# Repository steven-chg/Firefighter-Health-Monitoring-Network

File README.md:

# Firefighter Health Monitoring Network

A wearable health monitoring system that enables real-time tracking of firefighters' vital signs and environmental conditions during active duty. The system utilizes a mesh network of ESP32-based devices to continuously monitor and transmit critical health data including:

- Heart rate
- Motion 
- GPS location tracking
- Surrounding temperature measurements

## Key Features
- Wearable sensors integrated into firefighter gear
- Central monitoring hub for incident commanders with intuitive GUI 
- Real-time alerts for abnormal vital signs
- Mesh network with 300m+ urban range
- 2+ hour battery life in high temperature conditions

## Demo

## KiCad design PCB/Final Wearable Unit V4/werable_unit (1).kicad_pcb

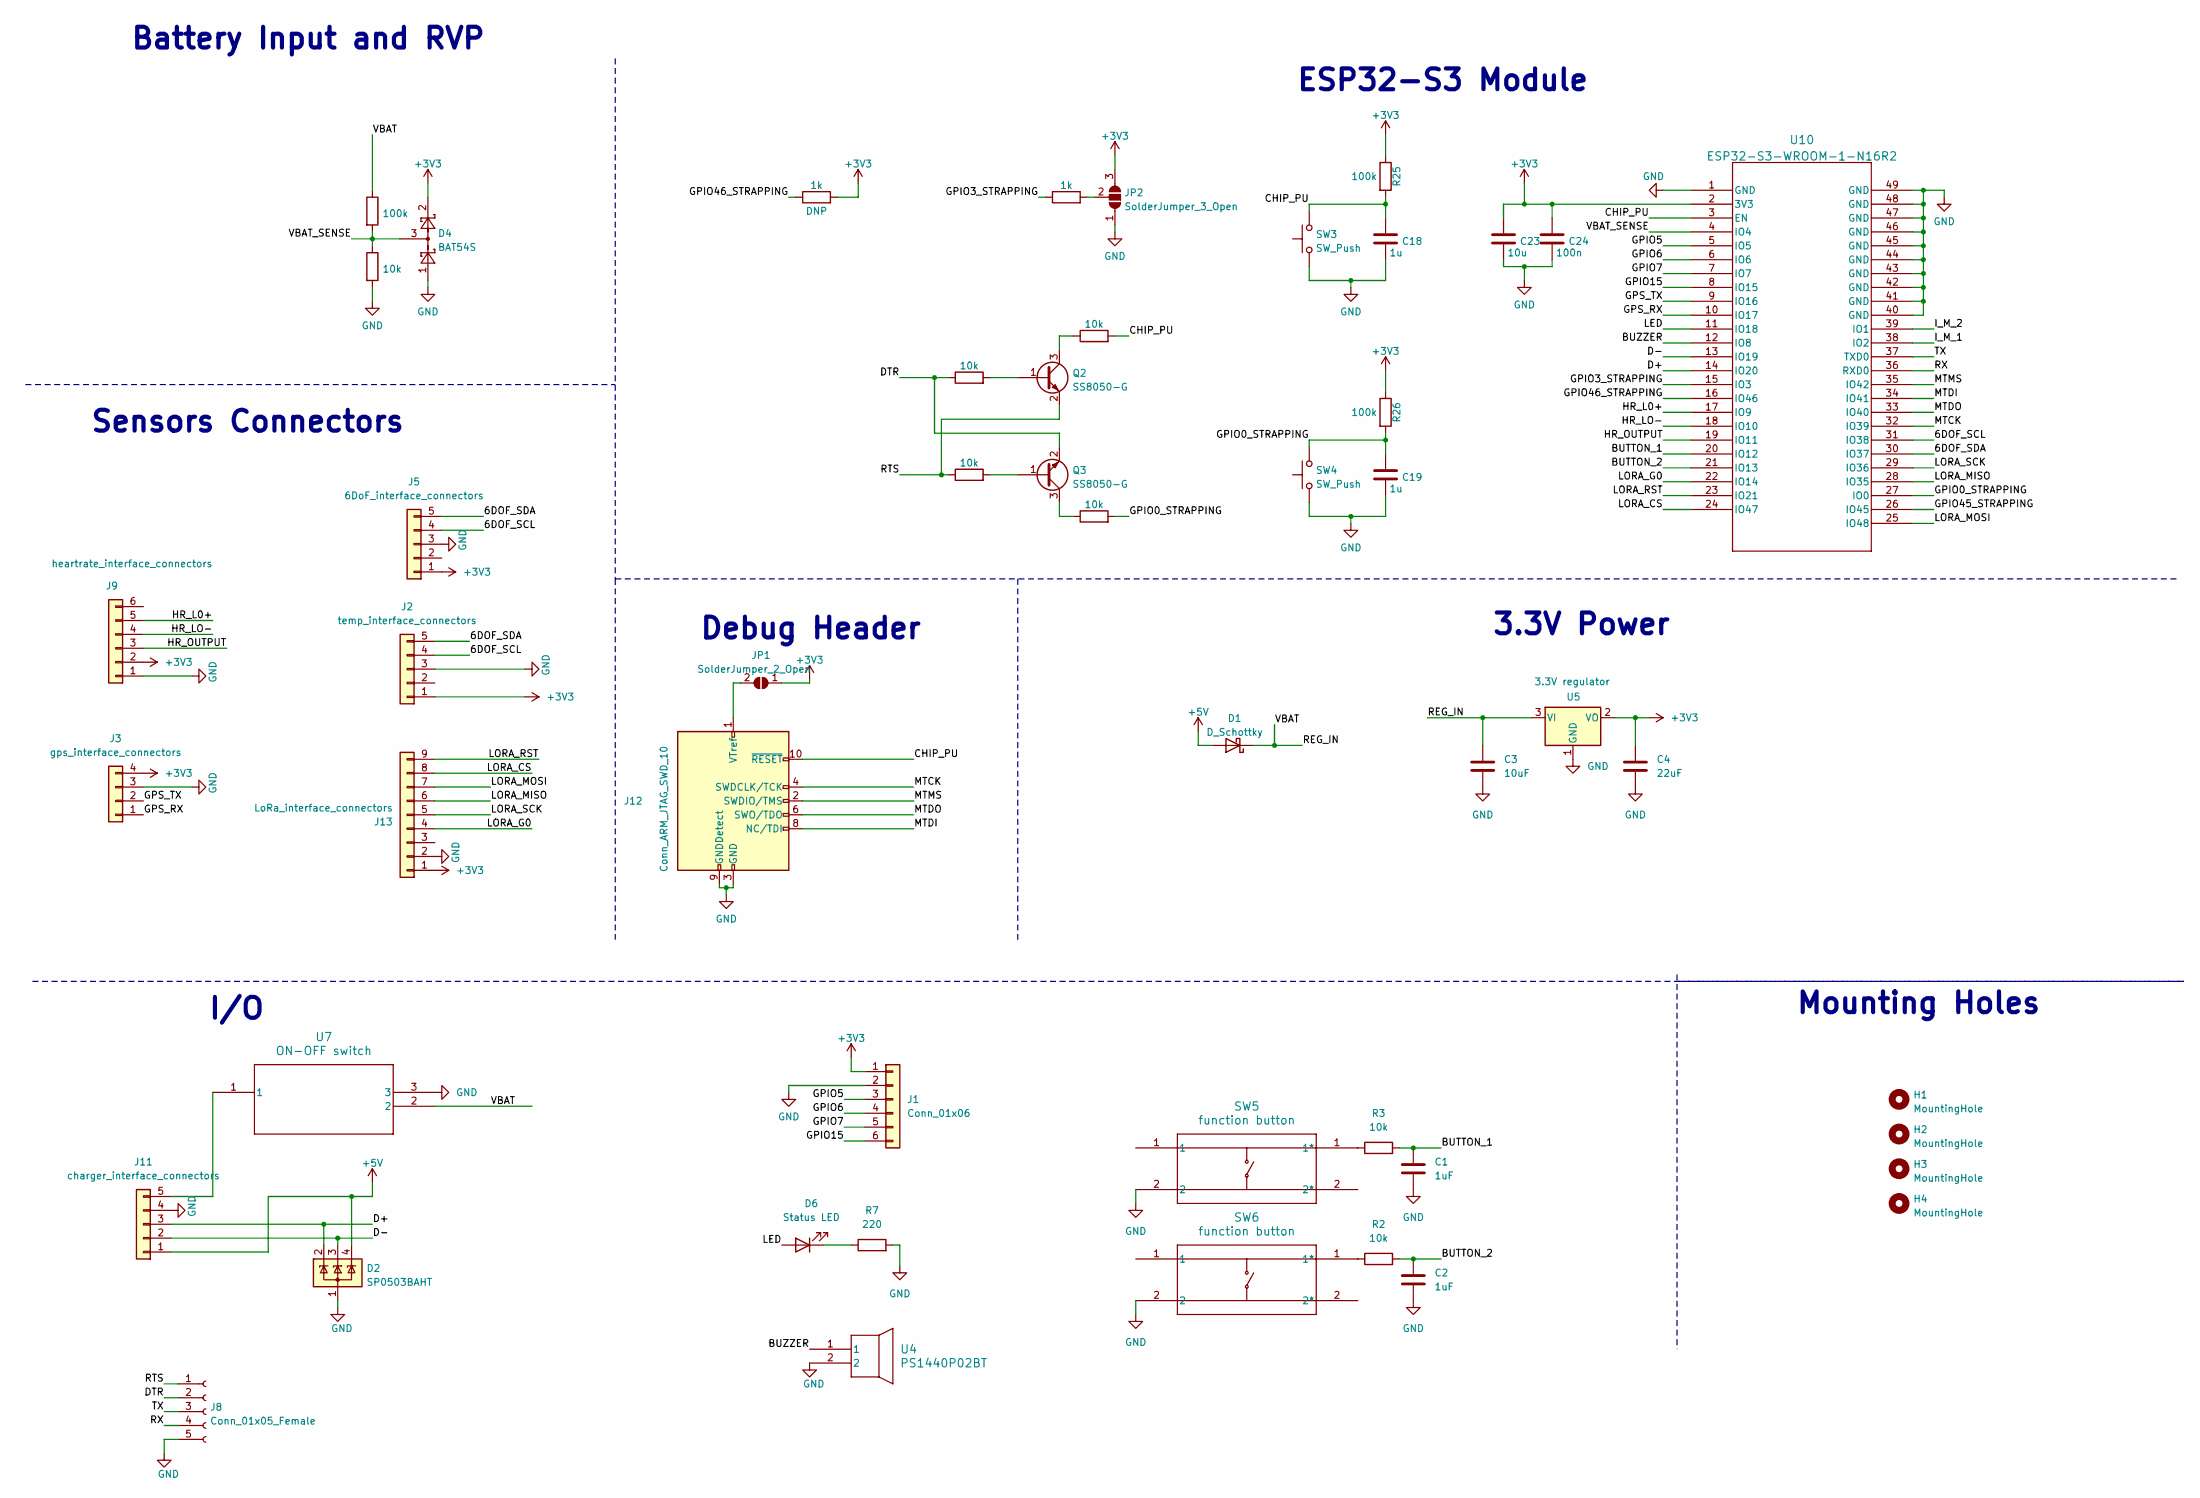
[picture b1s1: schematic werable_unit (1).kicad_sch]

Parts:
C1, C2: 1uF; C_0805_2012Metric_Pad1.18x1.45mm_HandSolder
C3: 10uF; C_0805_2012Metric_Pad1.18x1.45mm_HandSolder
C4: 22uF; C_0805_2012Metric_Pad1.18x1.45mm_HandSolder
C18, C19: 1u; C_0805_2012Metric_Pad1.18x1.45mm_HandSolder
C23: 10u; C_0805_2012Metric_Pad1.18x1.45mm_HandSolder
C24: 100n; C_0805_2012Metric_Pad1.18x1.45mm_HandSolder
D1: D_Schottky; D_SMA
D2: SP0503BAHT; SOT-143
D4: BAT54S; SOT-23
D6: Status LED; LED_1206_3216Metric
H1, H2, H3, H4: MountingHole; MountingHole_3.2mm_M3
J1: Conn_01x06; PinHeader_1x06_P2.54mm_Vertical
J2: temp_interface_connectors; PinHeader_1x05_P2.54mm_Vertical
J3: gps_interface_connectors; PinHeader_1x04_P2.54mm_Vertical
J5: 6DoF_interface_connectors; PinHeader_1x05_P2.54mm_Vertical
J8: Conn_01x05_Female; PinHeader_1x05_P2.54mm_Vertical
J9: heartrate_interface_connectors; PinHeader_1x06_P2.54mm_Vertical
J11: charger_interface_connectors; PinHeader_1x05_P2.54mm_Vertical
J12: Conn_ARM_JTAG_SWD_10; IDC-Header_2x05_P2.54mm_Vertical
J13: LoRa_interface_connectors; PinHeader_1x09_P2.54mm_Vertical
JP1: SolderJumper_2_Open; SolderJumper-2_P1.3mm_Open_TrianglePad1.0x1.5mm
JP2: SolderJumper_3_Open; SolderJumper-3_P2.0mm_Open_TrianglePad1.0x1.5mm
Q2, Q3: SS8050-G; SOT-23
R2, R3, R9, R14, R15, R19, R20: 10k; R_0805_2012Metric_Pad1.20x1.40mm_HandSolder
R7: 220; R_0805_2012Metric_Pad1.20x1.40mm_HandSolder
R8, R25, R26: 100k; R_0805_2012Metric_Pad1.20x1.40mm_HandSolder
R13, R18: 1k; R_0805_2012Metric_Pad1.20x1.40mm_HandSolder
SW3, SW4: SW_Push; SW_SPST_B3S-1000
SW5, SW6: function button; SW_SPST_EVQP7A
U4: PS1440P02BT; Buzzer_TDK_PS1240P02BT_D12.2mm_H6.5mm
U5: 3.3V regulator; TO-252-3_TabPin2
U7: ON-OFF switch; SW_Slide_SPDT_Angled_CK_OS102011MA1Q
U10: ESP32-S3-WROOM-1-N16R2; ESP32-S3-WROOM-1_EXP

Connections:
+3V3: C4.1, C23.1, C24.1, D4.2, J1.1, J2.1, J3.4, J5.1, J9.2 (3.3V), J13.1 (VIN), JP1.1 (A), JP2.3 (B), R13.2, R25.1, R26.1, U5.2 (VO), U10.2 (3V3)
+5V: D1.2 (A), D2.4 (K), J11.1 (5V)
/6DOF_SCL: J2.4, J5.4, U10.31 (IO38)
/6DOF_SDA: J2.5, J5.5, U10.30 (IO37)
/BUTTON_1: C1.1, R3.2, U10.20 (IO12)
/BUTTON_2: C2.1, R2.2, U10.21 (IO13)
/BUZZER: U4.1, U10.12 (IO8)
/CHIP_PU: C18.1, J12.10 (~RESET), R19.2, R25.2, SW3.2, U10.3 (EN)
/D+: D2.2 (K), J11.3 (D+), U10.14 (IO20)
/D-: D2.3 (K), J11.2 (D-), U10.13 (IO19)
/DTR: J8.2, Q3.2 (E), R14.1
/GPIO0_STRAPPING: C19.1, R20.2, R26.2, SW4.2, U10.27 (IO0)
/GPIO3_STRAPPING: R18.1, U10.15 (IO3)
/GPIO5: J1.3, U10.5 (IO5)
/GPIO6: J1.4, U10.6 (IO6)
/GPIO7: J1.5, U10.7 (IO7)
/GPIO15: J1.6, U10.8 (IO15)
/GPIO45_STRAPPING: U10.26 (IO45)
/GPIO46_STRAPPING: R13.1, U10.16 (IO46)
/GPS_RX: J3.1, U10.10 (IO17)
/GPS_TX: J3.2, U10.9 (IO16)
/HR_L0+: J9.5 (LO+), U10.17 (IO9)
/HR_LO-: J9.4 (LO-), U10.18 (IO10)
/HR_OUTPUT: J9.3 (OUTPUT), U10.19 (IO11)
/I_M_1: U10.38 (IO2)
/I_M_2: U10.39 (IO1)
/LED: D6.2 (A), U10.11 (IO18)
/LORA_CS: J13.8 (CS), U10.24 (IO47)
/LORA_G0: J13.4 (G0), U10.22 (IO14)
/LORA_MISO: J13.6 (MISO), U10.28 (IO35)
/LORA_MOSI: J13.7 (MOSI), U10.25 (IO48)
/LORA_RST: J13.9 (RST), U10.23 (IO21)
/LORA_SCK: J13.5 (SCK), U10.29 (IO36)
/MTCK: J12.4 (SWDCLK/TCK), U10.32 (IO39)
/MTDI: J12.8 (NC/TDI), U10.34 (IO41)
/MTDO: J12.6 (SWO/TDO), U10.33 (IO40)
/MTMS: J12.2 (SWDIO/TMS), U10.35 (IO42)
/RTS: J8.1, Q2.2 (E), R15.1
/RX: J8.4, U10.36 (RXD0)
/TX: J8.3, U10.37 (TXD0)
/VBAT_SENSE: D4.3, R8.2, R9.1, U10.4 (IO4)
GND: C1.2, C2.2, C3.2, C4.2, C18.2, C19.2, C23.2, C24.2, D2.1 (A), D4.1, J1.2, J2.3, J3.3, J5.3, J8.5, J9.1 (GND), J11.4 (GND), J12.3 (GND), J12.5 (GND), J12.9 (GNDDetect), J13.2 (GND), JP2.1 (A), R7.2, R9.2, SW3.1, SW4.1, SW5.2, SW6.2, U4.2, U5.1 (GND), U7.3, U10.1 (GND), U10.40 (GND), U10.41 (GND), U10.42 (GND), U10.43 (GND), U10.44 (GND), U10.45 (GND), U10.46 (GND), U10.47 (GND), U10.48 (GND), U10.49 (GND)
unnamed: D6.1 (K), R7.1
unnamed: J11.5 (BAT), U7.1
unnamed: J12.1 (VTref), JP1.2 (B)
unnamed: JP2.2 (C), R18.2
unnamed: Q2.1 (B), R14.2
unnamed: Q2.3 (C), R19.1
unnamed: Q3.1 (B), R15.2
unnamed: Q3.3 (C), R20.1
unnamed: R3.1, SW5.1 (1*)
unnamed: R2.1, SW6.1 (1*)

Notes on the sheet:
I/O
3.3V Power
Debug Header
ESP32-S3 Module
Mounting Holes
Sensors Connectors
Battery Input and RVP

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
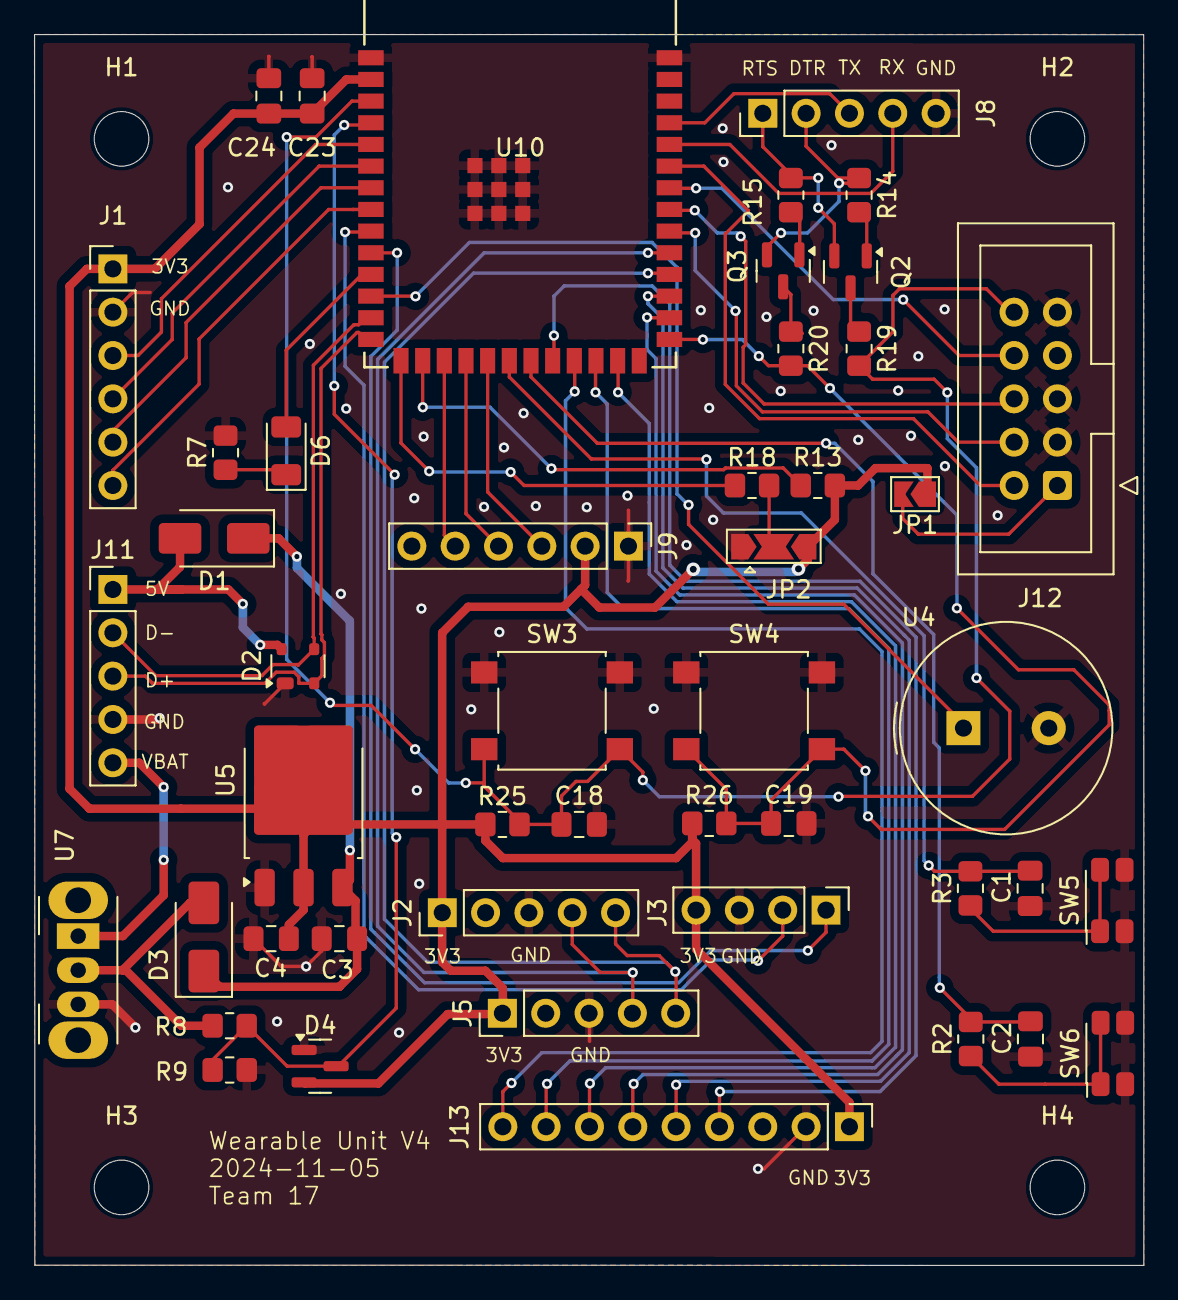
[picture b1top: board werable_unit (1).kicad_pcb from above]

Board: 2 copper layers, 65.0 x 72.2 mm, 51 parts (0 on the bottom side), 51 nets.

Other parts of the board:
D3: D_Schottky; D_SMA

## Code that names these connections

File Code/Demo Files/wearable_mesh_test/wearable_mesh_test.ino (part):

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Adafruit_LSM6DSO32 dso32;

// Define LoRa Pins
#define LORA_CS 47   // NSS (CS) pin
#define LORA_RST 21  // RST pin
#define LORA_IRQ 14  // DIO0 pin

// LoRa Network Settings
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
#define LO_PLUS_PIN 9
#define LO_MINUS_PIN 10
#define BUZZER_PIN 8
#define LED_BUILTIN 18

// Use hardware serial port 1 for GPS (ESP32 has multiple hardware UARTs)
#define GPS_RX 16  // Connect to GPS TX
#define GPS_TX 17  // Connect to GPS RX
HardwareSerial gpsSerial(1);  // Use UART1 for GPS
Adafruit_GPS GPS(&gpsSerial);
// Set GPSECHO to 'false' to turn off echoing the GPS data to the Serial console
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/////////////////////////////////////////////////////////////////////////////////////////////////////////////////////////////////////////////////////

// Battery Voltage
const int VBAT_SENSE_PIN = 4;  // GPIO pin 4 (ADC1_CH3) for battery sensing
const float DIVIDER_RATIO = 12.0;  // Voltage divider ratio (100k + 10k) / 10k = 11
const float ADC_REFERENCE = 3.3;  // ESP32 ADC reference voltage
const float ADC_RESOLUTION = 4095.0;  // ESP32 has 12-bit ADC (2^12 - 1)
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
  // Initialize LoRa
  SPI.begin(36, 35, 48, 47);  // Set SPI pins for LoRa
  LoRa.setPins(LORA_CS, LORA_RST, LORA_IRQ); // Set LoRa pins
  if (!LoRa.begin(915E6)) {    // Set frequency for North America
    Serial.println("LoRa initialization failed!");
    while (1);
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  // }

  // // GPS setup
  // gpsSerial.begin(9600, SERIAL_8N1, GPS_RX, GPS_TX);  // Initialize GPS with pins
  // GPS.begin(9600);  // Initialize GPS at 9600 baud
  // GPS.sendCommand(PMTK_SET_NMEA_OUTPUT_RMCGGA);  // Output RMC and GGA data
  // GPS.sendCommand(PMTK_SET_NMEA_UPDATE_1HZ);     // 1 Hz update rate
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  // Serial.println("GPS Initialized!");

  // // Buzzer Setup
  pinMode(BUZZER_PIN, OUTPUT); // configure GPIO8 as an output (can be set to high (buzzer on) or low (buzzer off)

  // LED Setup
  pinMode(LED_BUILTIN, OUTPUT);
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  
  // Take multiple samples
  for(int i = 0; i < NUM_SAMPLES; i++) {
    sum += analogRead(VBAT_SENSE_PIN);
    delay(10);  // Small delay between readings
  }
  
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  unsigned long endTime = millis() + duration;
  
  while(millis() < endTime) {
    digitalWrite(BUZZER_PIN, HIGH);
    delayMicroseconds(period / 2);
    digitalWrite(BUZZER_PIN, LOW);
    delayMicroseconds(period / 2);
  }
}
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
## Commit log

2024-10-22 project proposal and design document
2024-10-22 parts ordering forms
2024-10-22 added gps example code
2024-10-22 added hardwareserial gps
2024-10-22 updated parts order
2024-10-22 digikey order 2
2024-10-23 Lora Code
2024-11-06 order forms update
2024-11-06 adding heartrate, temperature, and accelerometer sketches
2024-11-20 change structure
2024-11-20 Add .gitignore file
2024-11-20 Remove .DS_Store files and add gitignore
2024-11-20 MeshNetwork and TFT Update
2024-11-20 adding sensor code
2024-11-21 updated code for final wearable unit
2024-11-21 wearable mesh update
2024-11-21 added
2024-11-21 wearable unit buzzer update
2024-12-02 final code update with heart rate
2024-12-03 final code update
2024-12-04 final demo
2024-12-14 document update
2024-12-14 design documents
2024-12-14 presentation update
2024-12-17 final version terminal code
